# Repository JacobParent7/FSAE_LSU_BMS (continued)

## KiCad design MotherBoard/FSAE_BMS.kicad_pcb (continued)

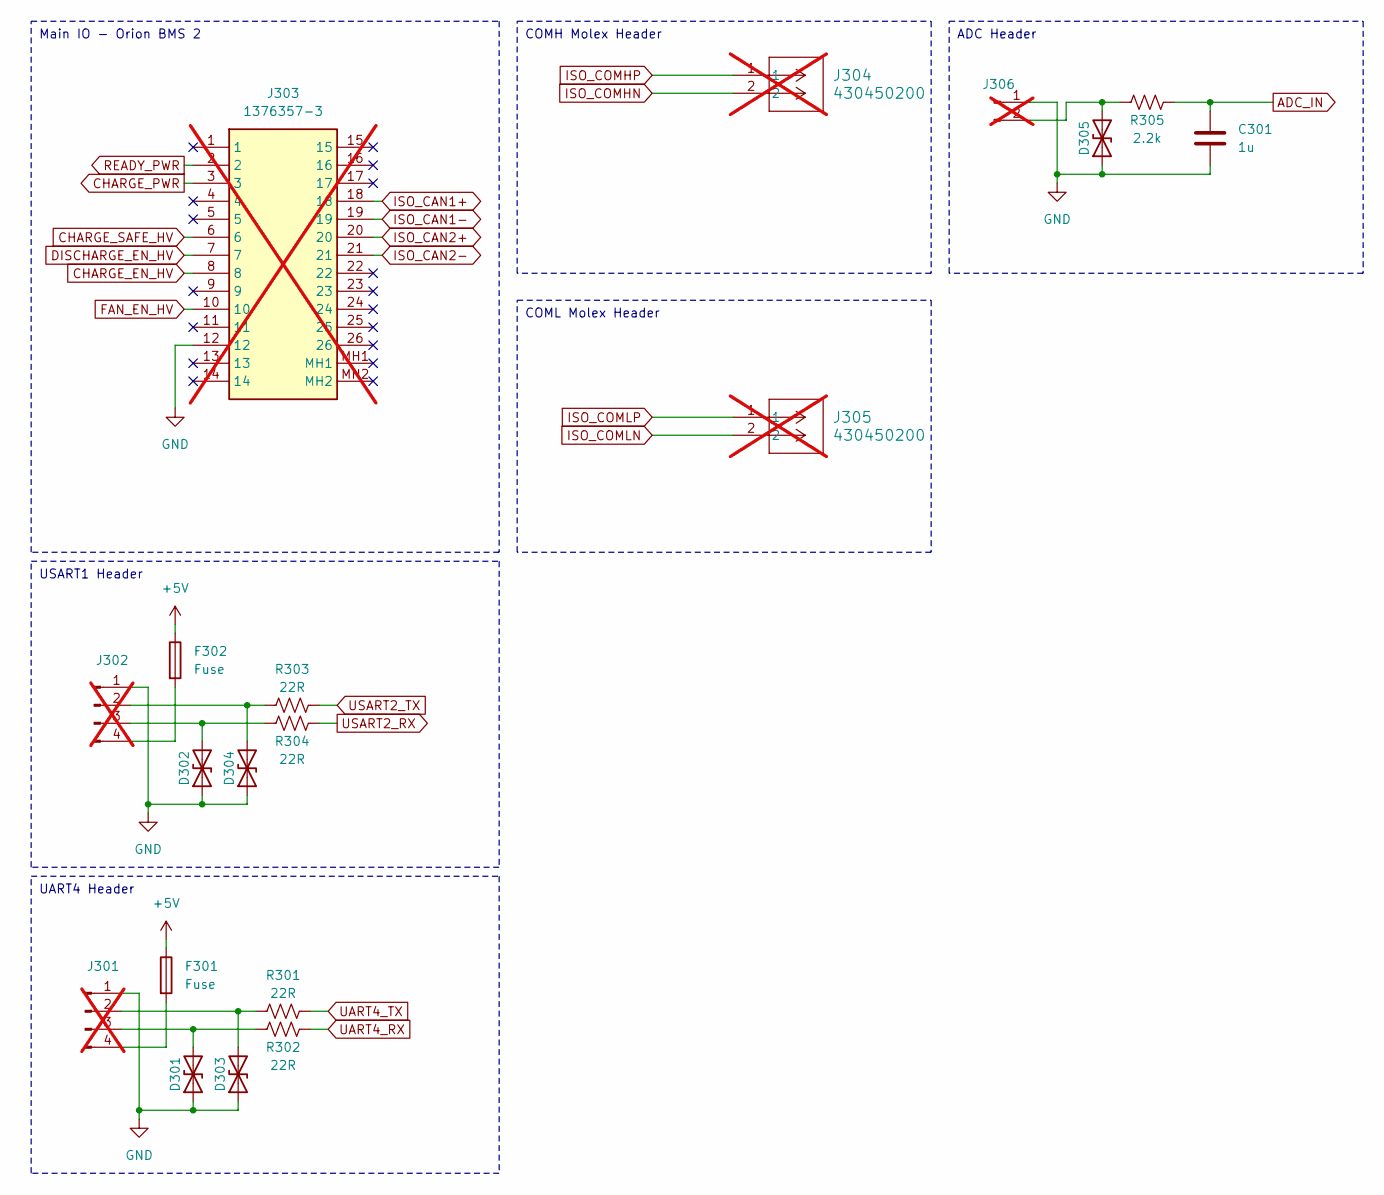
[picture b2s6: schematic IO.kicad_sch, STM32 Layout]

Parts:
C301: 1u; C_0402_1005Metric; Manufacturer_Part_Number CL05A105KO5NNNC; JLCPCB Part # C29266
D301, D302, D303, D304, D305: D_TVS; D_SOD-323; Manufacturer_Part_Number PESD3V3L1BA,115; JLCPCB Part # C51450
F301, F302: Fuse; Fuse_0805_2012Metric; Manufacturer_Part_Number SMD0805B050TF; JLCPCB Part # C269104
J301, J302: Conn_01x04_Pin; PinHeader_1x04_P2.54mm_Vertical; not fitted
J303: 1376357-3; 13763573; Mouser Part Number 571-1376357-3; not fitted
J304, J305: 430450200; CON_430450200_MOL; not fitted
J306: Conn_01x02_Pin; PinHeader_1x02_P2.54mm_Vertical; not fitted
R301, R302, R303, R304: 22R; R_1206_3216Metric; Manufacturer_Part_Number FRC1206J220 TS; JLCPCB Part # C2907457
R305: 2.2k; R_1206_3216Metric; Manufacturer_Part_Number 1206W4J0222T5E; JLCPCB Part # C26038

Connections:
+5V: F301.1, F302.1; also elsewhere on the board
ADC_IN: C301.1, R305.2; also elsewhere on the board
CHARGE_EN_HV: J303.8; also elsewhere on the board
CHARGE_PWR: J303.3; also elsewhere on the board
CHARGE_SAFE_HV: J303.6; also elsewhere on the board
DISCHARGE_EN_HV: J303.7; also elsewhere on the board
FAN_EN_HV: J303.10; also elsewhere on the board
GND: C301.2, D301.1 (A1), D302.1 (A1), D303.1 (A1), D304.1 (A1), D305.1 (A1), J301.1, J302.1, J303.12, J306.1; also elsewhere on the board
ISO_CAN1+: J303.18; also elsewhere on the board
ISO_CAN1-: J303.19; also elsewhere on the board
ISO_CAN2+: J303.20; also elsewhere on the board
ISO_CAN2-: J303.21; also elsewhere on the board
ISO_COMHN: J304.2; also elsewhere on the board
ISO_COMHP: J304.1; also elsewhere on the board
ISO_COMLN: J305.2; also elsewhere on the board
ISO_COMLP: J305.1; also elsewhere on the board
unnamed: D301.2 (A2), J301.3, R302.1
unnamed: D302.2 (A2), J302.3, R304.1
unnamed: D303.2 (A2), J301.2, R301.1
unnamed: D304.2 (A2), J302.2, R303.1
unnamed: D305.2 (A2), J306.2, R305.1
unnamed: F301.2, J301.4
unnamed: F302.2, J302.4
READY_PWR: J303.2; also elsewhere on the board
UART4_RX: R302.2; also elsewhere on the board
UART4_TX: R301.2; also elsewhere on the board
USART2_RX: R304.2; also elsewhere on the board
USART2_TX: R303.2; also elsewhere on the board

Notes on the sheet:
UART4 Header
Main IO - Orion BMS 2
COML Molex Header
COMH Molex Header
ADC Header
USART1 Header

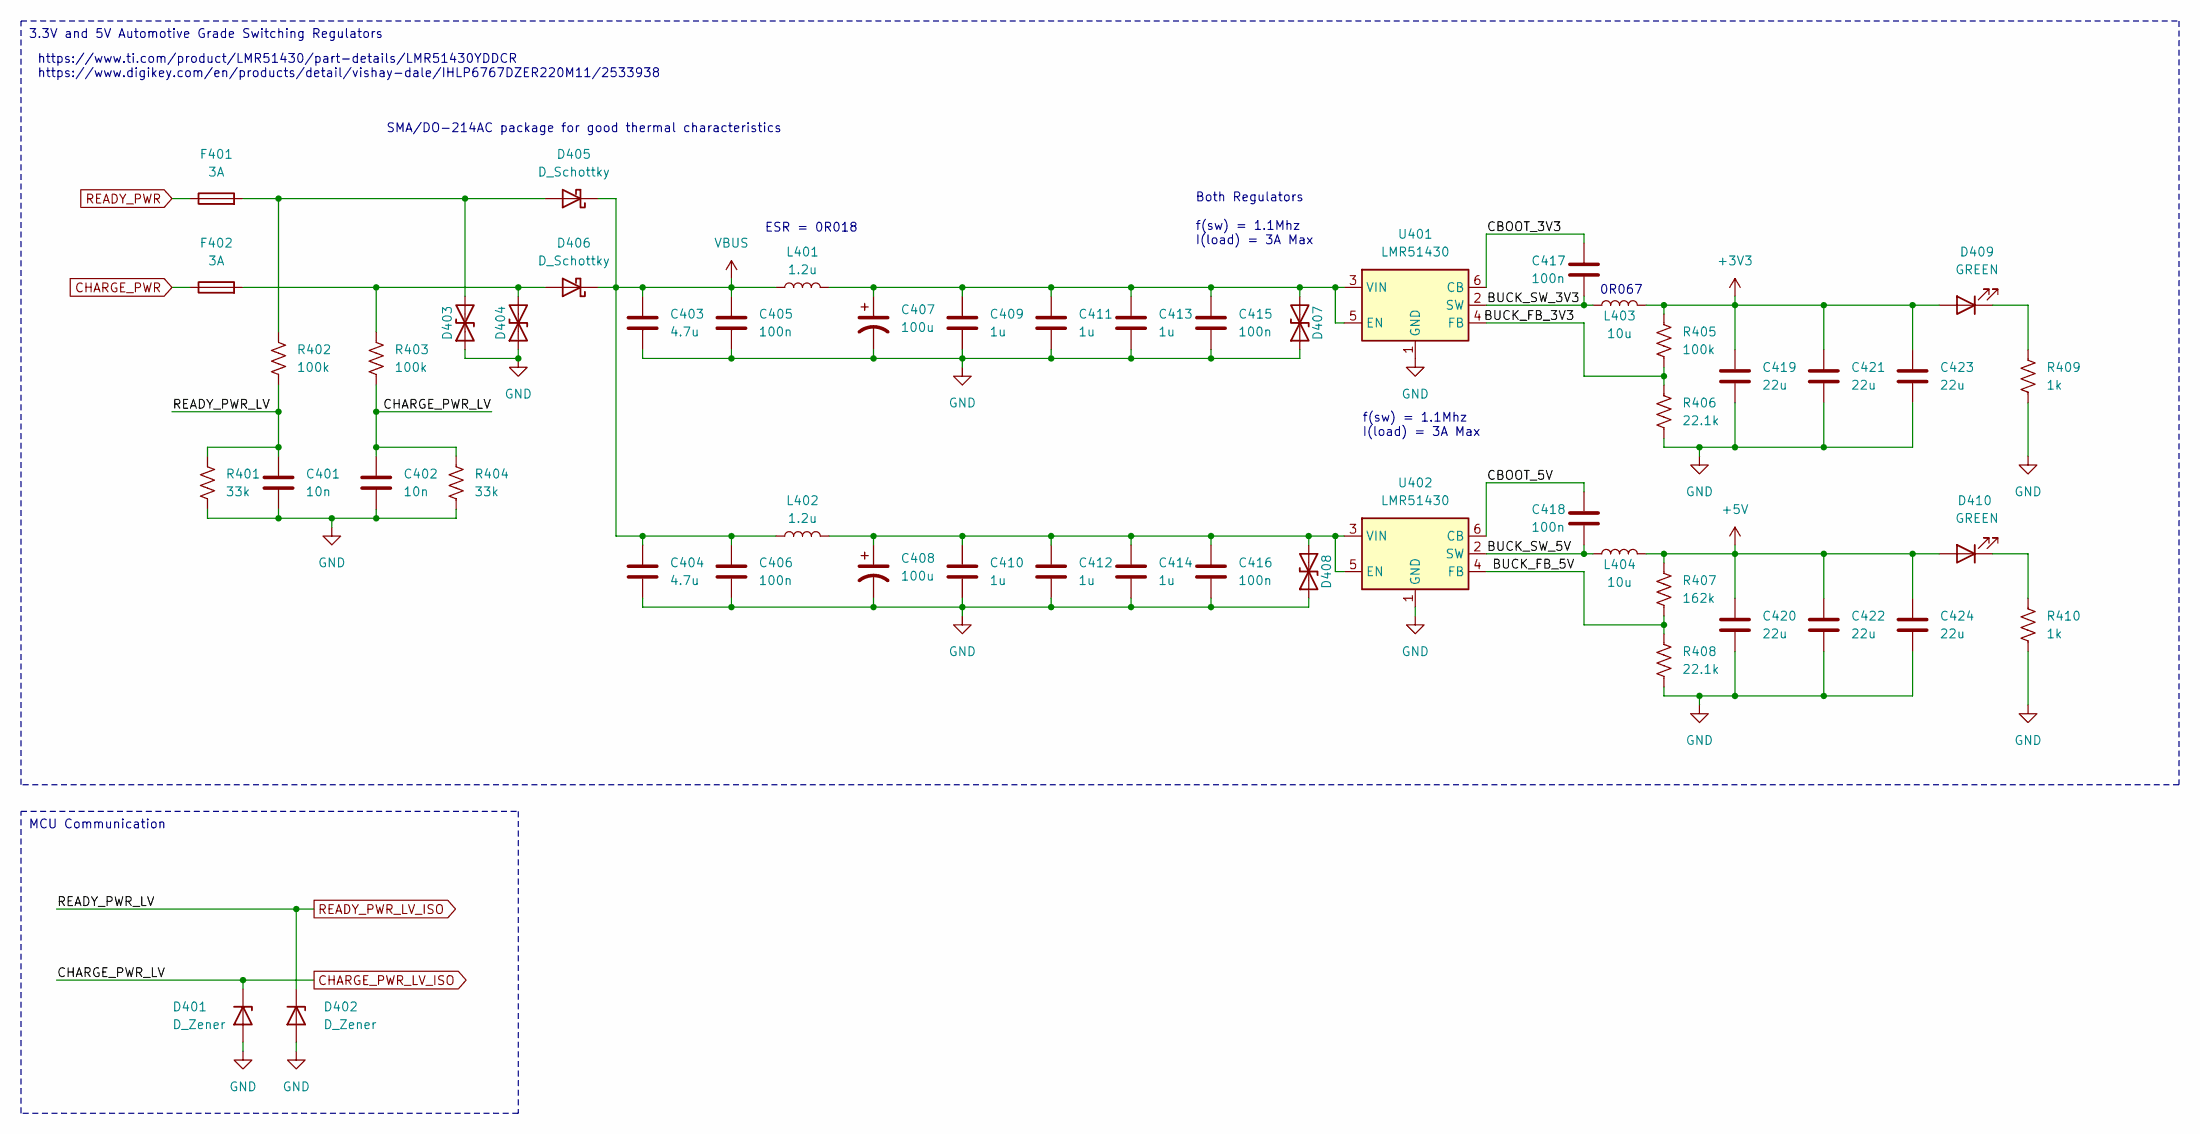
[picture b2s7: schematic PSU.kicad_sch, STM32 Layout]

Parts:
C401, C402: 10n; C_0402_1005Metric; Manufacturer_Part_Number CC0402KRX7R9BB103; JLCPCB Part # C60133
C403, C404: 4.7u; C_1206_3216Metric; Manufacturer_Part_Number 1206B475K500NT; JLCPCB Part # C29823
C405, C406, C415, C416, C417, C418: 100n; C_0402_1005Metric; Manufacturer_Part_Number CL05B104KO5NNNC; JLCPCB Part # C1525
C407, C408: 100u; CP_Elec_6.3x5.8; Manufacturer_Part_Number EEEFT1V101AP; JLCPCB Part # C128464
C409, C410, C411, C412, C413, C414: 1u; C_0805_2012Metric; Manufacturer_Part_Number CL21B105KBFNNNE; JLCPCB Part # C28323
C419, C420, C421, C422, C423, C424: 22u; C_0805_2012Metric; Manufacturer_Part_Number CL21A226MAQNNNE; JLCPCB Part # C45783
D401, D402: D_Zener; D_SOD-323; Manufacturer_Part_Number LM3Z3V3T1G; JLCPCB Part # C46279
D403, D404, D407, D408: D_TVS; D_SOD-123; Manufacturer_Part_Number SMF12CA; JLCPCB Part # C353317
D405, D406: D_Schottky; D_SMA; Manufacturer_Part_Number SS54; JLCPCB Part # C22452
D409, D410: GREEN; LED_0603_1608Metric; Manufacturer_Part_Number VLMTG1401-GS08; JLCPCB Part # C511604
F401, F402: 3A; Fuse_1206_3216Metric; Manufacturer_Part_Number 12H1300C; JLCPCB Part # C182445
L401, L402: 1.2u; L_Chilisin_BMRA00050530; Manufacturer_Part_Number BMRA000505301R2MA1; JLCPCB Part # C5296375
L403, L404: 10u; L_Sunlord_MWSA0603S; Manufacturer_Part_Number MWSA0603S-100MT; JLCPCB Part # C132141
R401, R404: 33k; R_0402_1005Metric; Manufacturer_Part_Number 0402WGF3302TCE; JLCPCB Part # C25779
R402, R403, R405: 100k; R_0402_1005Metric; Manufacturer_Part_Number 0402WGF1003TCE; JLCPCB Part # C25741
R406, R408: 22.1k; R_0402_1005Metric; Manufacturer_Part_Number 0402WGF2212TCE; JLCPCB Part # C43473
R407: 162k; R_0402_1005Metric; Manufacturer_Part_Number FRC0402F1623TS; JLCPCB Part # C2998128
R409, R410: 1k; R_0402_1005Metric; Manufacturer_Part_Number 0402WGF1001TCE; JLCPCB Part # C11702
U401, U402: LMR51430; SOT-23-6; Manufacturer_Part_Number LMR51430YDDCR; JLCPCB Part # C5210749

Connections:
+3V3: C419.1, C421.1, C423.1, D409.2 (A), L403.2, R405.1; also elsewhere on the board
+5V: C420.1, C422.1, C424.1, D410.2 (A), L404.2, R407.1; also elsewhere on the board
/PSU/BUCK_FB_3V3: R405.2, R406.1, U401.4 (FB)
/PSU/BUCK_FB_5V: R407.2, R408.1, U402.4 (FB)
/PSU/BUCK_SW_3V3: C417.2, L403.1, U401.2 (SW)
/PSU/BUCK_SW_5V: C418.2, L404.1, U402.2 (SW)
/PSU/CBOOT_3V3: C417.1, U401.6 (CB)
/PSU/CBOOT_5V: C418.1, U402.6 (CB)
CHARGE_PWR: F402.1; also elsewhere on the board
CHARGE_PWR_LV_ISO: C402.1, D401.1 (K), R403.2, R404.1; also elsewhere on the board
GND: C401.2, C402.2, C403.2, C404.2, C405.2, C406.2, C407.2, C408.2, C409.2, C410.2, C411.2, C412.2, C413.2, C414.2, C415.2, C416.2, C419.2, C420.2, C421.2, C422.2, C423.2, C424.2, D401.2 (A), D402.2 (A), D403.1 (A1), D404.1 (A1), D407.1 (A1), D408.1 (A1), R401.2, R404.2, R406.2, R408.2, R409.2, R410.2, U401.1 (GND), U402.1 (GND); also elsewhere on the board
unnamed: D403.2 (A2), D405.2 (A), F401.2, R402.1
unnamed: D404.2 (A2), D406.2 (A), F402.2, R403.1
unnamed: C407.1, C409.1, C411.1, C413.1, C415.1, D407.2 (A2), L401.2, U401.3 (VIN), U401.5 (EN)
unnamed: C408.1, C410.1, C412.1, C414.1, C416.1, D408.2 (A2), L402.2, U402.3 (VIN), U402.5 (EN)
unnamed: D409.1 (K), R409.1
unnamed: D410.1 (K), R410.1
READY_PWR: F401.1; also elsewhere on the board
READY_PWR_LV_ISO: C401.1, D402.1 (K), R401.1, R402.2; also elsewhere on the board
VBUS: C403.1, C404.1, C405.1, C406.1, D405.1 (K), D406.1 (K), L401.1, L402.1; also elsewhere on the board

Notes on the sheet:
MCU Communication
3.3V and 5V Automotive Grade Switching Regulators
https://www.ti.com/product/LMR51430/part-details/LMR51430YDDCR https://www.digikey.com/en/products/detail/vishay-dale/IHLP6767DZER220M11/2533938
f(sw) = 1.1Mhz I(load) = 3A Max
ESR = 0R018
0R067
Both Regulators f(sw) = 1.1Mhz I(load) = 3A Max
SMA/DO-214AC package for good thermal characteristics

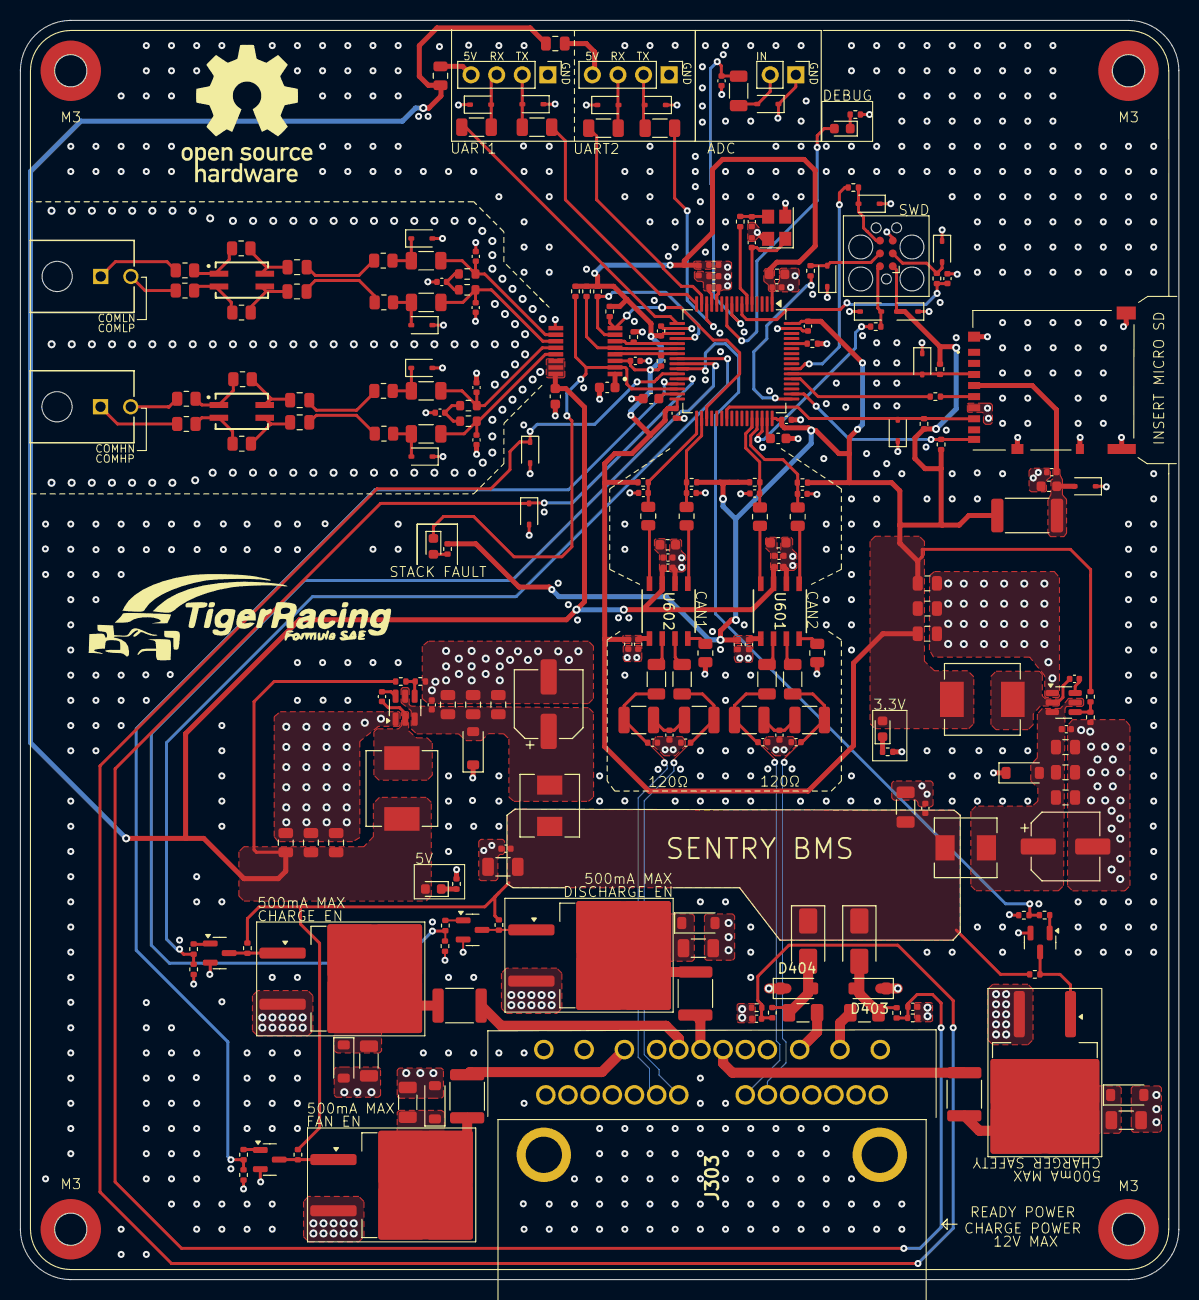
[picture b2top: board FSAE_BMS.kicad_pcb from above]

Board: 4 copper layers, 115.0 x 125.0 mm, 237 parts (0 on the bottom side), 129 nets.

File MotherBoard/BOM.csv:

"Reference","Value","Datasheet","Footprint","Qty","DNP","Manufacturer_Part_Number"
"C201,C216,C614,C619,C701,C702,C703,C704","10u","~","-- mixed values --","8","","-- mixed values --"
"C202,C205","10p","~","Capacitor_SMD:C_0402_1005Metric","2","","GRM1555C1H100FA01D"
"C203,C204,C206,C208,C210,C213,C215,C405,C406,C415,C416,C417,C418,C611,C612,C616,C617","100n","~","Capacitor_SMD:C_0402_1005Metric","17","","CL05B104KO5NNNC"
"C207,C209","2u2","~","Capacitor_SMD:C_0603_1608Metric","2",""," 0603B225K250NT"
"C211,C401,C402,C501,C502","10n","~","Capacitor_SMD:C_0402_1005Metric","5","","CC0402KRX7R9BB103"
"C212,C214,C301,C409,C410,C411,C412,C413,C414,C613,C615,C618,C620","1u","~","-- mixed values --","13","","-- mixed values --"
"C403,C404","4.7u","~","Capacitor_SMD:C_1206_3216Metric","2","","1206B475K500NT"
"C407,C408","100u","~","Capacitor_SMD:CP_Elec_6.3x5.8","2","","EEEFT1V101AP"
"C419,C420,C421,C422,C423,C424","22u","~","Capacitor_SMD:C_0805_2012Metric","6","","CL21A226MAQNNNE"
"C503,C504,C505,C506","100p","~","Capacitor_SMD:C_0402_1005Metric","4","","0402CG101J500NT"
"C507,C508,C513","220n","~","-- mixed values --","3","","-- mixed values --"
"C509,C510,C511,C512","2200p","~","Capacitor_SMD:C_0805_2012Metric","4","","CL21C222JBFNNNE"
"C601,C602,C605,C610","20p","~","Capacitor_SMD:C_0402_1005Metric","4","","0402CG200J500NT"
"C603,C604","4.7n","~","Capacitor_SMD:C_0402_1005Metric","2","","CC0402JRX7R9BB472"
"C606,C607,C608,C609","20pf","~","Capacitor_SMD:C_0402_1005Metric","4","","0402CG200J500NT"
"D201,D203,D204,D205,D206,D207,D208,D209,D301,D302,D303,D304,D305,D403,D404,D407,D408,D502,D503,D504,D505","D_TVS","~","-- mixed values --","21","","-- mixed values --"
"D202,D409,D410","GREEN","~","LED_SMD:LED_0603_1608Metric","3","","VLMTG1401-GS08"
"D401,D402","D_Zener","~","Diode_SMD:D_SOD-323","2","","LM3Z3V3T1G"
"D405,D406","D_Schottky","~","Diode_SMD:D_SMA","2","","SS54"
"D501","RED","~","LED_SMD:LED_0603_1608Metric","1","","KT-0603R"
"D701,D702,D703,D704","40V","~","Diode_SMD:D_SOD-123","4",""," BZT52C30"
"F301,F302","Fuse","~","Fuse:Fuse_0805_2012Metric","2","","SMD0805B050TF"
"F401,F402","3A","~","Fuse:Fuse_1206_3216Metric","2","","12H1300C"
"IC501","BQ79600PWRQ1","https://www.arrow.com/en/products/bq79600pwrq1/texas-instruments","BQ79600:BQ79600","1","","BQ79600PWRQ1"
"J202","DM3AT-SF-PEJM5_40_","https://componentsearchengine.com/Datasheets/2/DM3AT-SF-PEJM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","SDIO:SD_CARD","1","",""
"J301,J302","Conn_01x04_Pin","~","Connector_PinHeader_2.54mm:PinHeader_1x04_P2.54mm_Vertical","2","",""
"J303","1376357-3","https://www.te.com/commerce/DocumentDelivery/DDEController?A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","13763573","1","","1376357-3"
"J304,J305","430450200","430450200","molex_comm:CON_430450200_MOL","2","",""
"J306","Conn_01x02_Pin","~","Connector_PinHeader_2.54mm:PinHeader_1x02_P2.54mm_Vertical","1","",""
"L201","10n","~","Inductor_SMD:L_0402_1005Metric","1","","LQG15HN10NJ02D"
"L401,L402","1.2u","~","Inductor_SMD:L_Chilisin_BMRA00050530","2",""," BMRA000505301R2MA1"
"L403,L404","10u","~","Inductor_SMD:L_Sunlord_MWSA0603S","2","","MWSA0603S-100MT"
"L501,L502","WE-SLM","","WE-SLM:WE-SLM","2","","744242471"
"Q701,Q702,Q703,Q707","Q_NPN_BEC","~","Package_TO_SOT_SMD:SOT-23","4","","MMBT3904"
"Q704,Q705,Q706,Q708","Q_NMOS_GDS","~","Package_TO_SOT_SMD:TO-263-2","4","","IRF3205STRLPBF"
"R201,R409,R410,R501","1k","~","Resistor_SMD:R_0402_1005Metric","4","","0402WGF1001TCE"
"R202,R208,R209,R212,R507,R508,R509,R514,R601,R602,R607,R608,R701,R702,R703,R704,R705,R706,R710,R711","10k","~","Resistor_SMD:R_0402_1005Metric","20","","0402WGF1001TCE"
"R203,R211,R516,R517,R518,R519,R524,R525,R526,R527,R603,R604,R605,R606,R613,R614,R615,R616,R617,R618","0R","~","-- mixed values --","20","","-- mixed values --"
"R204,R205,R206,R207,R210,R301,R302,R303,R304","22R","~","-- mixed values --","9","","-- mixed values --"
"R305","2.2k","~","Resistor_SMD:R_1206_3216Metric","1","","FRC1206J220 TS"
"R401,R404","33k","~","Resistor_SMD:R_0402_1005Metric","2",""," 0402WGF3302TCE"
"R402,R403,R405,R506,R515,R707,R708,R709,R712","100k","~","Resistor_SMD:R_0402_1005Metric","9","","0402WGF1003TCE"
"R406,R408","22.1k","~","Resistor_SMD:R_0402_1005Metric","2","","0402WGF2212TCE"
"R407","162k","~","Resistor_SMD:R_0402_1005Metric","1","","FRC0402F1623TS"
"R502,R503,R504,R505","499","~","Resistor_SMD:R_0603_1608Metric","4","","0603WAF4990T5E"
"R510,R511,R512,R513","51","~","Resistor_SMD:R_1206_3216Metric","4","","C18019"
"R520,R521,R522,R523","0R","~","Resistor_SMD:R_0805_2012Metric","4","DNP","0805W8F0000T5E"
"R609,R610,R611,R612","60.4","~","Resistor_SMD:R_1210_3225Metric","4","","AC1210FR-0760R4L"
"U201","STM32F205RBTx","https://www.st.com/resource/en/datasheet/stm32f205rb.pdf","Package_QFP:LQFP-64_10x10mm_P0.5mm","1","","STM32F205RBT6"
"U401,U402","LMR51430","https://www.ti.com/lit/ds/symlink/lmr51430.pdf","Package_TO_SOT_SMD:SOT-23-6","2","","LMR51430YDDCR"
"U601,U602","PTCAN1462DRQ1","PTCAN1462DRQ1","CAN1462:CAN1462","2","","TCAN1462VDRQ1"
"Y201","16 Mhz","~","Crystal:Crystal_SMD_3225-4Pin_3.2x2.5mm","1","","X322516MLB4SI"

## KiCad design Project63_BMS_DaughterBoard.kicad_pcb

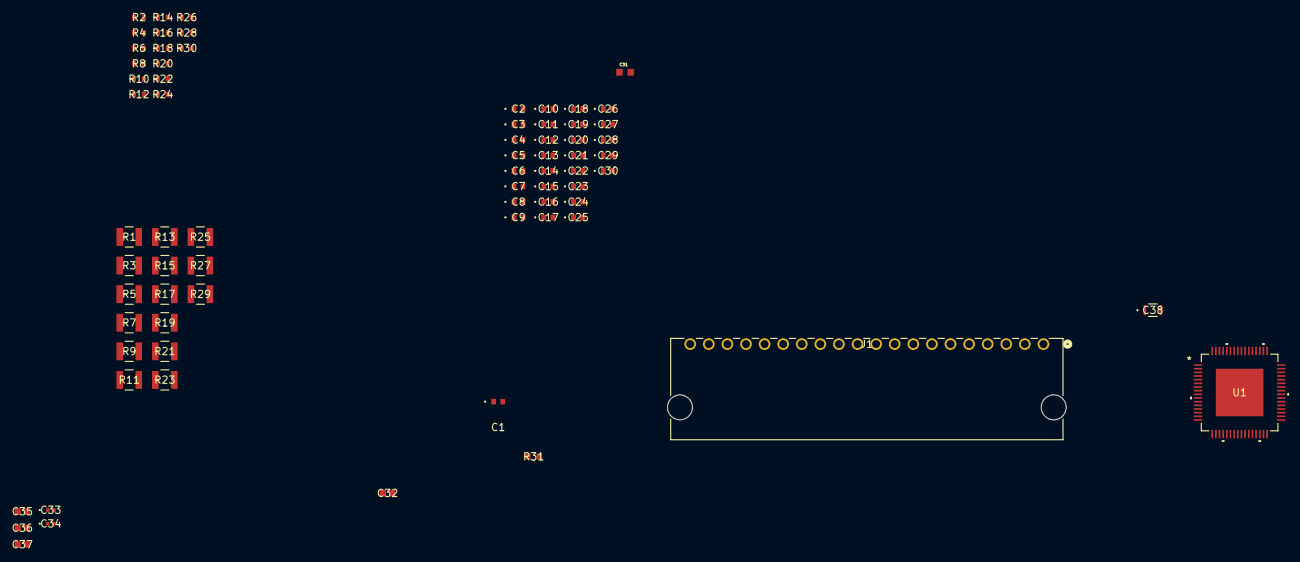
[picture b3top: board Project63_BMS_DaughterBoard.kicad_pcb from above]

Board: 2 copper layers, 71 parts (0 on the bottom side), 57 nets, no tracks yet.

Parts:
C1, C2, C3, C4, C5, C6, C7, C8, C9, C10, C11, C12, C13, C14, C15, C16, C17, C18, C19, C20, C21, C22, C23, C24, C25, C26, C27, C28, C29, C30: 0.47uF; G-188_MUR-L
C31: 10nF; CAPC1608X90N
C32, C35, C36, C37: 1uF; CAPC18095_95N_KEM-L
C33, C34: 0.1uF; CAP_GCM15_1p05X0p55X0p55_MUR-L
C38: 4.7uF; CAP_2012_TDK-L
J1: 705550019; CONN_705550019_MOL
R1, R3, R5, R7, R9, R11, R13, R15, R17, R19, R21, R23, R25, R27, R29: 10 Ohm; RC1210N_VIS-L
R2, R4, R6, R8, R10, R12, R14, R16, R18, R20, R22, R24, R26, R28, R30: 100 Ohm; RC0603N_PAN-L
R31: 30 Ohm; RC0603N_PAN
U1: BQ79614PAPRQ1; QFP_4PAPRQ1_TEX-L

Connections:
AVDD: C35.2, U1.38
AVSS: U1.36, U1.39, U1.46, U1.50, U1.EPAD
CB0: C1.2, C3.1, R1.1, U1.34
CB1: C3.2, C5.1, R3.1, U1.32
CB2: C5.2, C7.1, R5.1, U1.30
CB3: C7.2, C9.1, R7.1, U1.28
CB4: C9.2, C11.1, R9.1, U1.26
CB5: C11.2, C13.1, R11.1, U1.24
CB6: C13.2, C15.1, R13.1, U1.22
CB7: C15.2, C17.1, R15.1, U1.20
CB8: C17.2, C19.1, R17.1, U1.18
CB9: C19.2, C21.1, R19.1, U1.16
CB10: C21.2, C23.1, R21.1, U1.14
CB11: C23.2, C25.1, R23.1, U1.12
CB12: C25.2, C27.1, R25.1, U1.10
CB13: C27.2, C29.1, R27.1, U1.8
CB14: C29.2, R29.1, U1.6
CVDD: C38.2, U1.45
Cell 0: J1.1, J1.3, J1.4, J1.20, R1.2, R2.2
Cell 1: J1.5, R3.2, R4.2
Cell 2: J1.6, R5.2, R6.2
Cell 3: J1.7, R7.2, R8.2
Cell 4: J1.8, R9.2, R10.2
Cell 5: J1.9, R11.2, R12.2
Cell 6: J1.10, R13.2, R14.2
Cell 7: J1.11, R15.2, R16.2
Cell 8: J1.12, R17.2, R18.2
Cell 9: J1.13, R19.2, R20.2
Cell 10: J1.14, R21.2, R22.2
Cell 11: J1.15, R23.2, R24.2
Cell 12: J1.16, R25.2, R26.2
Cell 13: J1.17, R27.2, R28.2
Cell 14: J1.2, J1.19
Cell 14S: J1.18, R29.2, R30.2
DVDD: C37.2, U1.49
GND_AVSS: C1.1, C2.1, C31.1, C35.1
GND_CVSS: C32.1, C33.1, C34.1
LDOIN: C34.2, U1.47
NEG5V: C33.2, U1.44
unnamed: C31.2, R31.1, U1.1
REFHP: C36.2, U1.37
TSREF: C32.2, U1.51
VC0: C2.2, C4.1, R2.1, U1.35
VC1: C4.2, C6.1, R4.1, U1.33
VC2: C6.2, C8.1, R6.1, U1.31
VC3: C8.2, C10.1, R8.1, U1.29
VC4: C10.2, C12.1, R10.1, U1.27
VC5: C12.2, C14.1, R12.1, U1.25
VC6: C14.2, C16.1, R14.1, U1.23
VC7: C16.2, C18.1, R16.1, U1.21
VC8: C18.2, C20.1, R18.1, U1.19
VC9: C20.2, C22.1, R20.1, U1.17
VC10: C22.2, C24.1, R22.1, U1.15
VC11: C24.2, C26.1, R24.1, U1.13
VC12: C26.2, C28.1, R26.1, U1.11
VC13: C28.2, C30.1, R28.1, U1.9
VC14: C30.2, R30.1, U1.7

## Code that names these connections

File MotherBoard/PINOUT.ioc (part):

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Mcu.Name=STM32F205R(B-C-E-F-G)Tx
Mcu.Package=LQFP64
Mcu.UserName=STM32F205RBTx
PA0-WKUP.Mode=Asynchronous
PA0-WKUP.Signal=UART4_TX
PA1.Mode=Asynchronous
PA1.Signal=UART4_RX
PA11.Mode=CAN_Activate
PA11.Signal=CAN1_RX
PA12.Mode=CAN_Activate
PA12.Signal=CAN1_TX
PA13.Mode=Trace_Asynchronous_SW
PA13.Signal=SYS_JTMS-SWDIO
PA14.Mode=Trace_Asynchronous_SW
PA14.Signal=SYS_JTCK-SWCLK
PA15.GPIOParameters=GPIO_Label
PA15.GPIO_Label=SDIO_DET
PA15.Signal=GPIO_Input
PA2.Mode=Asynchronous
PA2.Signal=USART2_TX
PA3.Mode=Asynchronous
PA3.Signal=USART2_RX
PA4.Mode=NSS_Signal_Hard_Output
PA4.Signal=SPI1_NSS
PA5.Mode=Full_Duplex_Master
PA5.Signal=SPI1_SCK
PA6.Mode=Full_Duplex_Master
PA6.Signal=SPI1_MISO
PA7.Mode=Full_Duplex_Master
PA7.Signal=SPI1_MOSI
PB0.GPIOParameters=GPIO_Label
PB0.GPIO_Label=CHARGE_SAFE_LV
PB0.Signal=GPIO_Output
PB1.GPIOParameters=GPIO_Label
PB1.GPIO_Label=CHARGE_PWR_LV_ISO
PB1.Signal=GPIO_Input
PB10.GPIOParameters=GPIO_Label
PB10.GPIO_Label=FAN_EN_LV
PB10.Signal=GPIO_Output
PB11.GPIOParameters=GPIO_Label
PB11.GPIO_Label=BQ_NFAULT
PB11.Signal=GPIO_Input
PB12.Mode=CAN_Activate
PB12.Signal=CAN2_RX
PB13.Mode=CAN_Activate
PB13.Signal=CAN2_TX
PB14.GPIOParameters=GPIO_Label
PB14.GPIO_Label=BQ_SPI_RDY
PB14.Signal=GPIO_Input
PB2.GPIOParameters=GPIO_Label
PB2.GPIO_Label=READY_PWR_LV_ISO
PB2.Signal=GPIO_Input
PB3.Mode=Trace_Asynchronous_SW
PB3.Signal=SYS_JTDO-SWO
PC1.Signal=ADCx_IN11
PC12.Mode=SD_1_bit
PC12.Signal=SDIO_CK
PC2.GPIOParameters=GPIO_Label
PC2.GPIO_Label=TEST_LED
PC2.Signal=GPIO_Output
PC4.GPIOParameters=GPIO_Label
PC4.GPIO_Label=CHARGE_EN_LV
PC4.Signal=GPIO_Output
PC5.GPIOParameters=GPIO_Label
PC5.GPIO_Label=DISCHARGE_EN_LV
PC5.Signal=GPIO_Output
PC8.Mode=SD_1_bit
PC8.Signal=SDIO_D0
PD2.Mode=SD_1_bit
PD2.Signal=SDIO_CMD
PH0-OSC_IN.Mode=HSE-External-Oscillator
PH0-OSC_IN.Signal=RCC_OSC_IN
PH1-OSC_OUT.Mode=HSE-External-Oscillator
PH1-OSC_OUT.Signal=RCC_OSC_OUT
RCC.HSE_VALUE=16000000
RCC.SYSCLKFreq_VALUE=120000000
RCC.SYSCLKSource=RCC_SYSCLKSOURCE_PLLCLK
board=custom

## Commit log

2024-09-29 Initial KiCAD Setup
    This is the initial project setup with an example of how to make the schematic design modular.
2024-10-01 Initial daughter board setup
2024-10-03 Initial MOBO Upload
2024-10-10 Add files via upload
    Updated KiCAD schematics for Daughter Board. (10/10/24)
2024-10-15 Added IO and STM32 uC
2024-10-15 Added IO Connector and uC
2024-10-17 Daughter_Board Update 2
    -Added some 3d models before fall break. (10/17/2024)
2024-10-17 DaughterBoard Update 2
2024-10-22 Added new README
2024-10-22 Test 2
2024-10-27 modhy commit
2024-10-31 90% DOBO is done
2024-11-02 NPN is done
2024-11-04 Complete bootstrap schematic for MCU
2024-11-05 I think all componets for DOBO schematic are added, wired and assigned to their footprints. Next step to work on ERC
2024-11-06 Test Commit
2024-11-07 Daughter Update
2024-11-09 11/9/2024
2024-11-11 DOBO ERC 139 warnings left
2024-11-15 PSU Complete
2024-11-17 Reviewing
2024-11-22 ready for pcb
2024-11-23 only fuses left
2024-11-24 Fuse
2024-11-27 Starting Routing
2024-11-28 C:/Program Files/Git/
2024-11-28 test
2024-11-28 Layout continued. Fixed Footprint and most 3d model
2024-11-30 tracing left
2024-12-05 Connectors
2024-12-11 Added BQ7900 rough draft and TCAN
2024-12-14 layout
2025-01-09 Fixed BQ79600 + minor changes
2025-01-10 Fixed CAN tranceivers + added relay driver circuit + fixed relative file paths for 3D models + finished PSU but still need correct 3D model
2025-01-11 Revised all schematics + completed relay driver page
2025-01-13 Fixed 3D model paths. Finished PSU ORing shcematic.
2025-01-13 Added more 3D models
2025-01-17 Fixed relative paths + 90% footprints done + organized PCB for layout + found JLC part #s for manufacturing
2025-01-18 done
2025-01-20 Initial Routing
2025-01-20 Completed BOM except inductors
2025-01-21 Redesigned EMI filters for switching regulators to meet CISPR 25 Class 5 EMI constraint + substituted BOM #s for JLC basic parts
2025-01-21 BOM completed + All 3D models added + Initial board shape complete
2025-01-21 Routing update 2
2025-01-26 Finished MCU + Tranceiver layout
2025-01-27 Layout 90% complete
2025-01-28 Layout complete for regulators and relay drivers
2025-02-01 Routing Update 3
2025-02-01 Finished layout need to route
2025-02-03 Finished motherboard. Need to review BOM
2025-02-03 Fixed power routing mistake + finished BOM + generated manufacturing files
2025-02-04 Silkscreen edits
2025-02-09 Reworked ground planes
2025-02-10 Finished board
2025-02-10 Daughterboard 100% Complete + Edited Motherboard BOM
2025-02-10 Test-point silk screen edits complete
2025-02-11 Both boards complete
2025-02-25 Firmware init
2025-03-13 LED Blinky
2025-03-20 CAN peripheral working
2025-04-02 Initial BQ79600 -> BQ79616 communication
2025-04-10 Autoaddressing Firmware Working
2025-04-15 Voltage reading function
2025-04-15 Updating SPI frame write function
2025-04-17 Fixes to voltage read - NOT WORKING
2025-04-17 voltage read working
2025-04-20 ADC Working
2025-04-22 Voltage stack read working + Vdelta calculation for balancing
2025-04-25 SOC and balancing working
